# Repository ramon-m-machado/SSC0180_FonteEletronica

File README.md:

# Projeto da Fonte

## Sumário
[Integrantes](#Integrantes) <br />
[Objetivo](#objetivo) <br />
[Links](#links) <br />
[Função de cada componente](#funcao) <br />
[Componentes](#Componentes) <br />
[Cálculos](#calculos) <br />
[Circuito no Falstad](#falstad) <br />
[Circuito no Eagle](#eagle) <br />
[Circuito PCB](#pcb) <br />

## Integrantes
<h4> Ramon Moreira Machado - Nº USP 12543179 <br />
Victor Lucas de Almeida Fernandes - Nº USP 12675399 </h4>

## Objetivo do trabalho
Partindo de uma tomada com corrente alternada de 127V (pico de 179,6V)
e frequência de 60 Hz, construir uma fonte retificadora que consiga deixar 
a corrente contínua e ajustar a tensão para valores entre 3V e 12V.

## Links
[Vídeo explicativo](https://drive.google.com/file/d/1JKtw4jIEJxu9kp_Ld9PL_cwXYOSiDElz/view?usp=sharing) <br />
[Circuito no Falstad](https://tinyurl.com/yhs23wuz)

## Função de cada componente

* **Transformador:** 
responsável pela redução da tensão que chega da tomada. O transformador
escolhido é capaz de modificar a ddp de 127V, com pico de 179,6V, para 12V, com pico de 17,287V. Como a tensão máxima 
da fonte é de 12V, escolhemos um valorde pico superior para garantir que esse resultado
consiga ser obtido, visto que os componentes do circuito consomem tensão.

* **Ponte de diodos:** 
responsável pela retificação do circuito, ou seja, por inverter o 
semiciclo negativo da corrente alternada. Assim, o circuito é abastecido com a corrente 
em ambos os semiciclos da corrente. No entanto, ainda existe variação na tensão, decorrente
da troca entre os semiciclos.

* **Capacitor:** 
responsável pela etapa de filtragem. 
O capacitor é capaz de armazenar uma determinada carga, e como o seu tempo de descarga é maior
do que o período do sinal de entrada, ele alimenta o circuito quando a corrente passa do pico e diminui 
significativamente e é recarregado durante o aumento da corrente até chegar no pico. 
Assim, ele consegue diminuir a variação de tensão no circuito, o "Ripple".

* **Resistores:**
responsáveis pelo controle da corrente que passa pelo circuito, 
evitando que os outros componentes queimem.

* **Diodo Zener:**
responsável por regular a tensão máxima do circuito. A tensão escolhida para o Zener foi de 13V, porque 
outros componentes ainda vão consumir tensão, e o valor máximo da fonte precisa ser de 12V. 
Assim, se a tensão que chega no Zener for superior a 13V, ele deixa a corrente passar com tensão de 13V.
Se for inferior a 13V, ele não influencia no circuito.

* **Potenciômetro:**
responsável pela regulação da tensão entre 3 e 12V.

* **Transistor NPN**:
responsável pela "regulação" da corrente elétrica.

## Cálculos

## Componentes

| Componente | Especificação | Valor |
| --- | --- | --- |
| Transformador | 12V | [R$26,99][transformador]|`R$ x`|
| Ponte de Diodos | 1N4007 | [R$0,10 x 4 = R$0,40][diodos] | |
| Capacitor | 1000uF | [R$0,79][capacitor] | |
| Resistor | 1kΩ | [R$0,05][resistor1] |
| Resistor | 820Ω | [R$0,05][resistor2] |
| Resistor | 4k7Ω | [R$0,05][resistor3] |
| Led | 5mm | [R$0,25][led]| |
| Diodo Zener | 13V | [R$0,19][zener]| |
| Potenciômetro | 10k | [R$1,79][potenciometro] | |
| Transistor | NPN | [R$0,29][npn]| |

[transformador]: https://produto.mercadolivre.com.br/MLB-989883391-transformador-trafo-1212v-200ma-bivolt-eletronica-eletrica-_JM?quantity=1#position=1&type=item&tracking_id=9abf8c61-6492-4e02-bb1d-d1a22f9b055d
[diodos]: https://www.baudaeletronica.com.br/diodo-1n4007.html
[capacitor]: https://www.baudaeletronica.com.br/capacitor-eletrolitico-1000uf-25v.html?gclid=CjwKCAjwgISIBhBfEiwALE19SV9PtG2yy8U5UN-H_dH_FWmCW822ftNFBUs8vyb2IieIiflBTjFcrRoCpP0QAvD_BwE
[led]: https://www.baudaeletronica.com.br/led-difuso-5mm-vermelho.html
[zener]: https://www.baudaeletronica.com.br/diodo-zener-1n4743-13v-1w.html?gclid=CjwKCAjwgISIBhBfEiwALE19SRW7bm8yXdRT0GTHfEzPJIUN8f9VPnWAHMp7ED1Eef8v-AIL5G_f7RoC4P0QAvD_BwE
[potenciometro]: https://www.baudaeletronica.com.br/potenciometro-linear-de-10k-10000.html?gclid=CjwKCAjwgISIBhBfEiwALE19SfFnNJtX0-Vd7lZdZ-2e183X3vlfUzLg71sWm2MVyKX1NRZIPBpZ1BoC5EsQAvD_BwE
[npn]: https://www.baudaeletronica.com.br/transistor-npn-2n2222.html?gclid=CjwKCAjwgISIBhBfEiwALE19SU9pQN6ihh4v9VTW-1ot3MlpanbD9w5BCGmXj4O_K-mzTs0KxVAMlRoClfwQAvD_BwE

[resistor1]: https://www.baudaeletronica.com.br/resistor-1k-5-1-4w.html
[resistor2]: https://www.baudaeletronica.com.br/resistor-820r-5-1-4w.html
[resistor3]: https://www.baudaeletronica.com.br/resistor-4k7-5-1-4w.html

## Circuito no Falstad

## Circuito no Eagle

## Circuito PCB

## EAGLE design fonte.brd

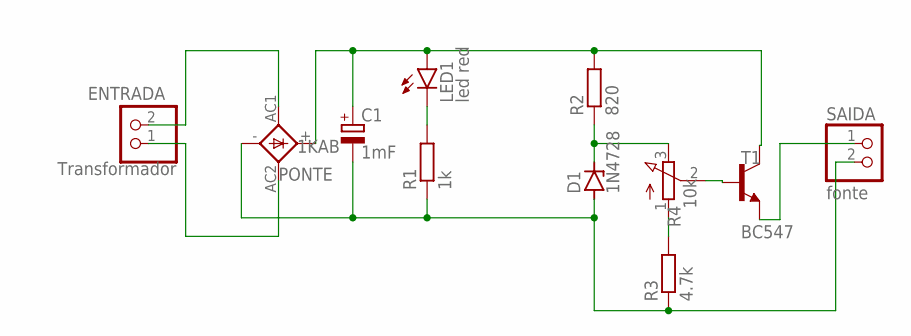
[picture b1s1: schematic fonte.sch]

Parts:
C1: 1mF; E5-10,5
D1: 1N4728; DO41Z10
ENTRADA: Transformador; 1X02
LED1: led red; LED5MM
PONTE: 1KAB
R1: 1k; 0207/10
R2: 820; 0207/10
R3: 4.7k; 0207/10
R4: 10k; 3RP/1610N
SAIDA: fonte; 1X02
T1: BC547; TO92

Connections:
unnamed: ENTRADA.2, PONTE.AC1
unnamed: ENTRADA.1, PONTE.AC2
unnamed: C1.-, D1.A, PONTE.-, R1.1, R3.1
unnamed: C1.+, LED1.A, PONTE.+, R2.2, T1.3 (C)
unnamed: LED1.K (C), R1.2
unnamed: D1.C, R2.1, R4.3 (E)
unnamed: R4.2 (S), T1.2 (B)
unnamed: SAIDA.1, T1.1 (E)
unnamed: R3.2, R4.1 (A)

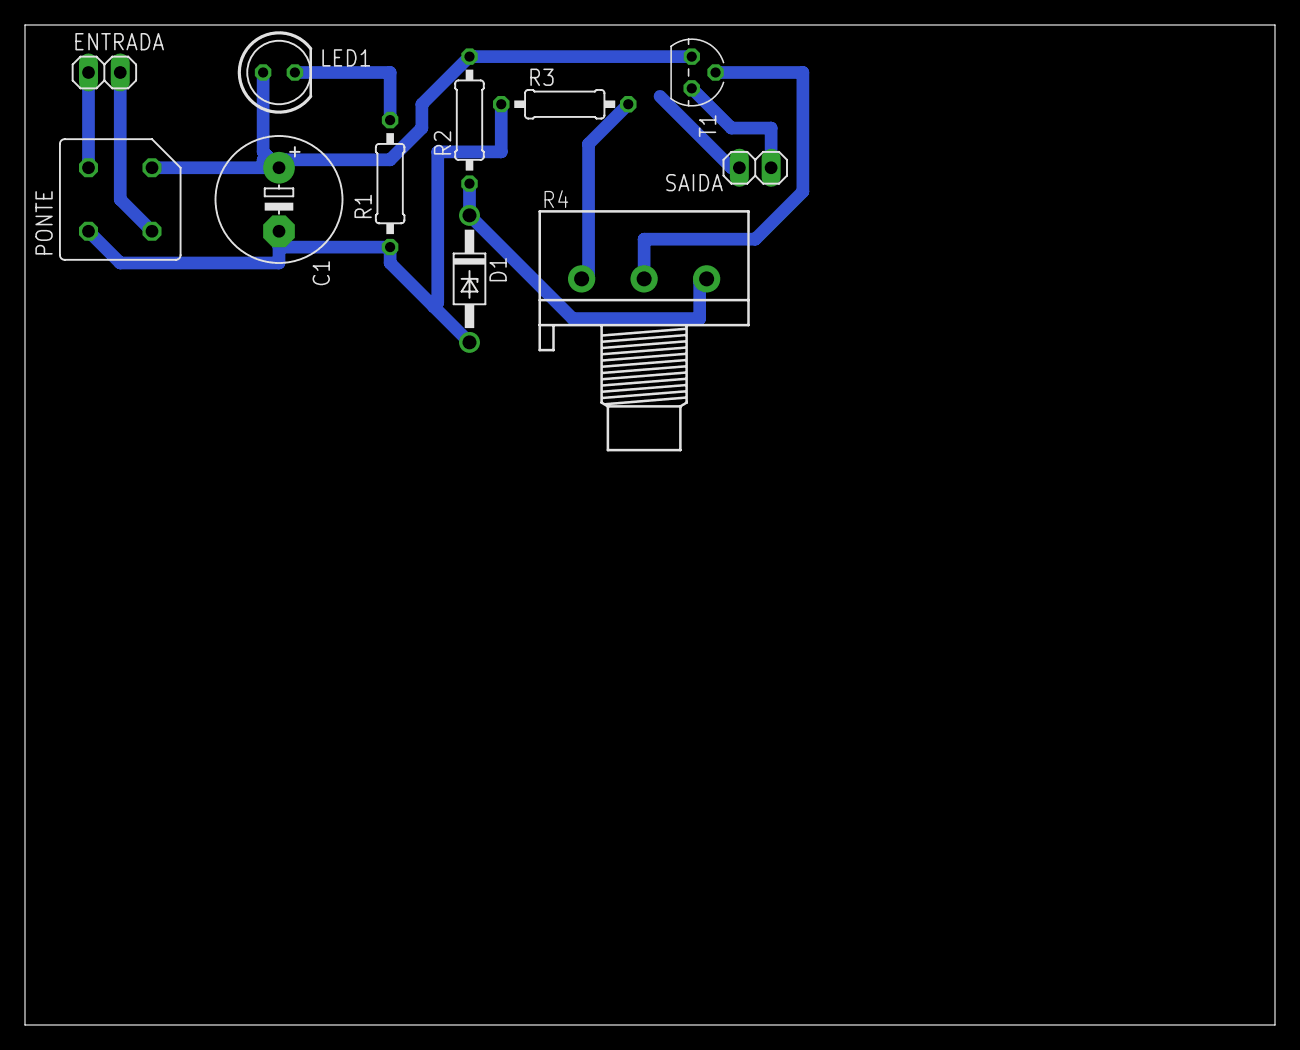
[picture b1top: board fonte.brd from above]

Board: 2 copper layers, 100.0 x 80.0 mm, 11 parts (0 on the bottom side), 9 nets.
